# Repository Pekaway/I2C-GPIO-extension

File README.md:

# I2C-GPIO-extension
I2C Extension for the VAN PI CORE

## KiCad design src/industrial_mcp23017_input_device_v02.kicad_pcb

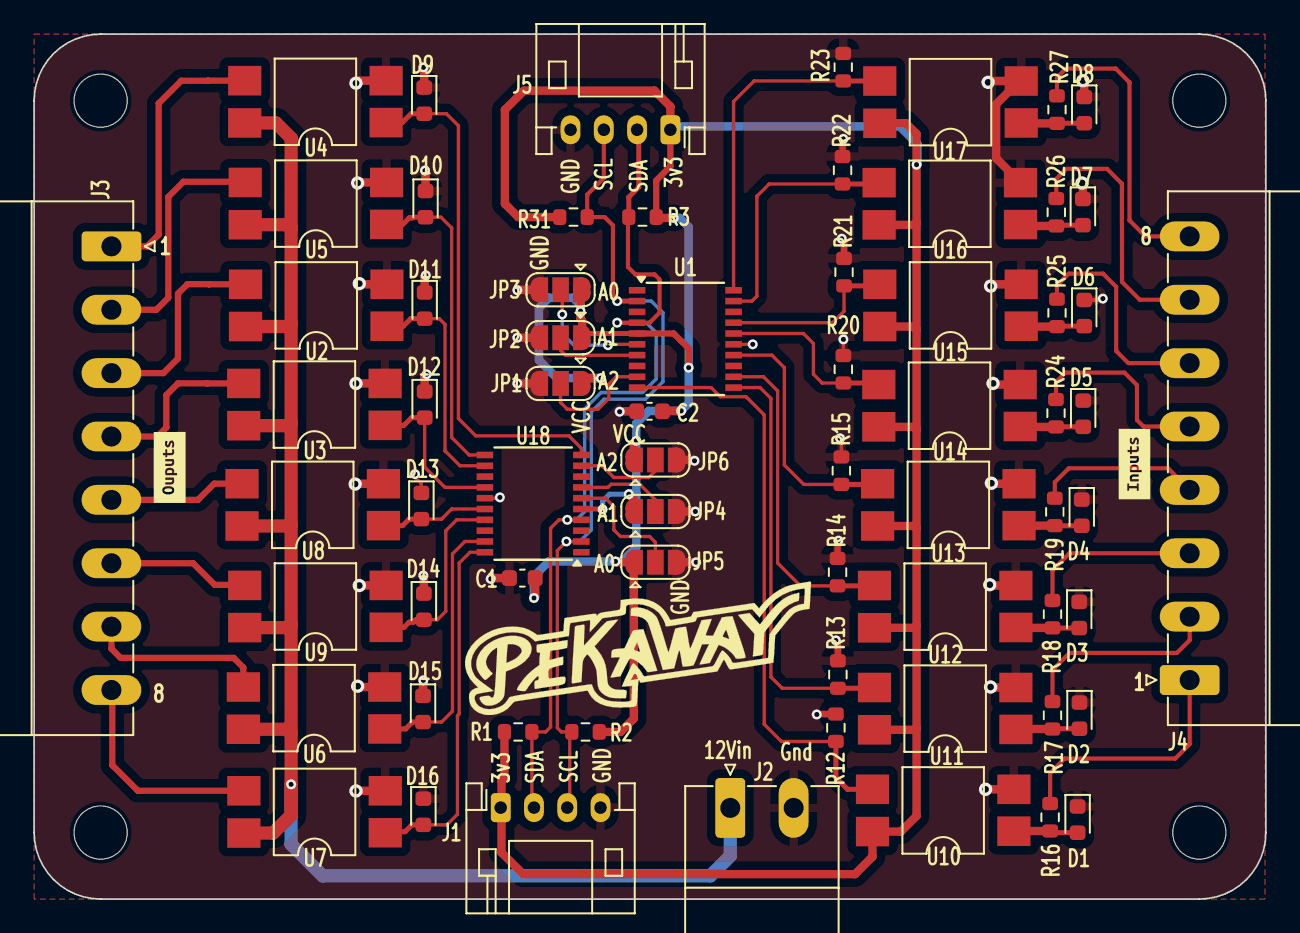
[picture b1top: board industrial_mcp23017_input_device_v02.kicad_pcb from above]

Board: 2 copper layers, 74.1 x 52.0 mm, 69 parts (0 on the bottom side), 51 nets.

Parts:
C1, C2: 0.1u; C_0603_1608Metric
D1, D2, D3, D4, D5, D6, D7, D8, D9, D10, D11, D12, D13, D14, D15, D16: LED_Small; LED_0603_1608Metric
J1, J5: Conn_01x04; JST_PH_S4B-PH-K_1x04_P2.00mm_Horizontal
J2: Conn_01x02; PhoenixContact_MC_1,5_2-G-3.81_1x02_P3.81mm_Horizontal
J3, J4: Conn_01x08; PhoenixContact_MC_1,5_8-G-3.81_1x08_P3.81mm_Horizontal
JP1, JP2, JP3, JP4, JP5, JP6: Jumper_3_Open; SolderJumper-3_P1.3mm_Open_RoundedPad1.0x1.5mm
R1, R2, R3, R12, R13, R14, R15, R20, R21, R22, R23, R31: 10k; R_0603_1608Metric
R16, R17, R18, R19, R24, R25, R26, R27: 4.7k; R_0603_1608Metric
U1, U18: PCF8574ATS; SSOP-20_4.4x6.5mm_P0.65mm
U2, U3, U4, U5, U6, U7, U8, U9, U10, U11, U12, U13, U14, U15, U16, U17: PC817; SMDIP-4_W7.62mm-updated
kibuzzard-63E0F99F: G***; kibuzzard-63E0F99F
kibuzzard-63E0F976: G***; kibuzzard-63E0F976

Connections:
+3V3: C1.1, C2.1, J1.1, J5.1, JP1.1 (A), JP2.1 (A), JP3.1 (A), JP4.1 (A), JP5.1 (A), JP6.1 (A), R1.1, R2.1, R3.1, R31.1, U1.5 (VDD), U10.4, U11.4, U12.4, U13.4, U14.4, U15.4, U16.4, U17.4, U18.5 (VDD)
+12V: J2.1, U2.4, U3.4, U4.4, U5.4, U6.4, U7.4, U8.4, U9.4
/Inputs/In1: R12.1, U1.10 (P0), U10.3
/Inputs/In2: R13.1, U1.11 (P1), U11.3
/Inputs/In3: R14.1, U1.12 (P2), U12.3
/Inputs/In4: R15.1, U1.14 (P3), U13.3
/Inputs/In5: R20.1, U1.16 (P4), U14.3
/Inputs/In6: R21.1, U1.17 (P5), U15.3
/Inputs/In7: R22.1, U1.19 (P6), U16.3
/Inputs/In8: R23.1, U1.20 (P7), U17.3
/Inputs/In_Trig1: J4.1, R16.2
/Inputs/In_Trig2: J4.2, R17.2
/Inputs/In_Trig3: J4.3, R18.2
/Inputs/In_Trig4: J4.4, R19.2
/Inputs/In_Trig5: J4.5, R24.2
/Inputs/In_Trig6: J4.6, R25.2
/Inputs/In_Trig7: J4.7, R26.2
/Inputs/In_Trig8: J4.8, R27.2
/outputs/OUT1: J3.1, U4.3
/outputs/OUT2: J3.2, U5.3
/outputs/OUT3: J3.3, U2.3
/outputs/OUT4: J3.4, U3.3
/outputs/OUT5: J3.5, U8.3
/outputs/OUT6: J3.6, U9.3
/outputs/OUT7: J3.7, U6.3
/outputs/OUT8: J3.8, U7.3
/outputs/out_trig1: D9.2 (A), U4.1, U18.10 (P0)
/outputs/out_trig2: D10.2 (A), U5.1, U18.11 (P1)
/outputs/out_trig3: D11.2 (A), U2.1, U18.12 (P2)
/outputs/out_trig4: D12.2 (A), U3.1, U18.14 (P3)
/outputs/out_trig5: D13.2 (A), U8.1, U18.16 (P4)
/outputs/out_trig6: D14.2 (A), U9.1, U18.17 (P5)
/outputs/out_trig7: D15.2 (A), U6.1, U18.19 (P6)
/outputs/out_trig8: D16.2 (A), U7.1, U18.20 (P7)
/scl: J1.3, J5.3, R2.2, R31.2, U1.2 (SCL), U18.2 (SCL)
/sda: J1.2, J5.2, R1.2, R3.2, U1.4 (SDA), U18.4 (SDA)
GND: C1.2, C2.2, D1.1 (K), D2.1 (K), D3.1 (K), D4.1 (K), D5.1 (K), D6.1 (K), D7.1 (K), D8.1 (K), D9.1 (K), D10.1 (K), D11.1 (K), D12.1 (K), D13.1 (K), D14.1 (K), D15.1 (K), D16.1 (K), J1.4, J2.2, J5.4, JP1.3 (B), JP2.3 (B), JP3.3 (B), JP4.3 (B), JP5.3 (B), JP6.3 (B), R12.2, R13.2, R14.2, R15.2, R20.2, R21.2, R22.2, R23.2, U1.15 (VSS), U2.2, U3.2, U4.2, U5.2, U6.2, U7.2, U8.2, U9.2, U10.2, U11.2, U12.2, U13.2, U14.2, U15.2, U16.2, U17.2, U18.15 (VSS)
unnamed: D1.2 (A), R16.1, U10.1
unnamed: D2.2 (A), R17.1, U11.1
unnamed: D3.2 (A), R18.1, U12.1
unnamed: D4.2 (A), R19.1, U13.1
unnamed: D5.2 (A), R24.1, U14.1
unnamed: D6.2 (A), R25.1, U15.1
unnamed: D7.2 (A), R26.1, U16.1
unnamed: D8.2 (A), R27.1, U17.1
unnamed: JP1.2 (C), U1.9 (A2)
unnamed: JP2.2 (C), U1.7 (A1)
unnamed: JP3.2 (C), U1.6 (A0)
unnamed: JP4.2 (C), U18.7 (A1)
unnamed: JP5.2 (C), U18.6 (A0)
unnamed: JP6.2 (C), U18.9 (A2)

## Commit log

2024-03-15 no message
